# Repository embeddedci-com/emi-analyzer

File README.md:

# EMI Analyzer

PCB EMI and EMC analysis on your own computer. Open a KiCad board or a zip of Gerber files and
see what to fix, marked on the board, in seconds.

| | |
|---|---|
| **Layout checks** | 23 checks: return paths, plane gaps and stitching, decoupling, impedance, length matching, differential pair routing, test point stubs, copper under antennas, thin power traces, ESD protection at connectors, shield grounding, reset lines, power input and switching-regulator layout. Each finding says what to do. |
| **Decoupling** | Per supply rail and IC: the impedance of its capacitors against a target, where it falls short, and which change closes the gap. |
| **ESD** | An IEC 61000-4-2 contact discharge into each line that leaves the board, simulated in ngspice, with the clamp where it is and moved to the connector. |
| **Cables** | How much common-mode current each connector's cable can carry before it passes the FCC limit, from an antenna model in nec2c. |
| **Part solve** | One net (or a pair) cut out over its planes and solved in openEMS in minutes: where its current flows and what its ends see. No far field, no compliance estimate, no coupling into neighboring nets, and no component models (those need `full-wave` and the openEMS the worker image ships). See [verification](docs/verification/small-part-solve.md). |
| **Versions** | Upload a changed layout as a new version and see which findings were fixed and which are new. |
| **Settings** | Turn checks on or off and set thresholds per board in the app, or in an `emi.rules.yaml` next to the board. |
| **Reports** | One HTML file (or PDF) with the board, findings and results, to share. |

Your boards and results stay on your computer. Nothing is uploaded anywhere.

Results are for comparing versions of your own board. They are not a pre-compliance test. See
[known issues](docs/known-issues.md).

Full-wave simulation of a whole region (openEMS) and conducted emissions are built but off. See
[experimental features](#experimental-features).

---

## Contents

1. [What you need](#what-you-need)
2. [Step 1: Install Docker](#step-1-install-docker)
3. [Step 2: Install EMI Analyzer](#step-2-install-emi-analyzer)
4. [Step 3: First launch](#step-3-first-launch)
5. [Step 4: Analyze a board](#step-4-analyze-a-board)
   - [Sharing results](#sharing-results)
6. [Using it from KiCad](#using-it-from-kicad)
7. [Using it from Claude Code](#using-it-from-claude-code)
8. [Running without the desktop app](#running-without-the-desktop-app)
9. [Running in the background](#running-in-the-background)
10. [Where your data is](#where-your-data-is)
11. [Updating and uninstalling](#updating-and-uninstalling)
12. [Troubleshooting](#troubleshooting)
13. [Experimental features](#experimental-features)
14. [More documentation](#more-documentation)

---

## What you need

| | |
|---|---|
| **Operating system** | macOS 11 or newer (Apple Silicon or Intel), Windows 10 or 11 (64-bit), or 64-bit Linux on x86-64 |
| **Memory** | 8 GB or more |
| **Disk** | About 4 GB free: 1.4 GB for the worker image, the rest for Docker and your results |
| **Docker** | Docker Desktop on macOS and Windows; Docker Engine or Docker Desktop on Linux |
| **Internet** | Only to download the app and, once per version, the worker image |

EMI Analyzer has two parts. The **app** is a small download that shows your boards and results.
The **worker** does the analysis. It runs inside Docker, so it behaves the same on every
operating system, and the app starts and stops it for you.

---

## Step 1: Install Docker

Skip this step if `docker ps` already works in a terminal.

### macOS

With [Homebrew](https://brew.sh), one command:

```bash
brew install --cask docker-desktop
```

Then continue at step 3. Without Homebrew:

1. Download **Docker Desktop for Mac** from
   <https://docs.docker.com/desktop/setup/install/mac-install/>. Choose **Apple Silicon** or
   **Intel** to match your Mac (Apple menu → *About This Mac* → *Chip* or *Processor*).
2. Open the downloaded `Docker.dmg` and drag **Docker** into **Applications**.
3. Open **Docker** from Applications. Accept the service agreement and, when asked, allow the
   helper with your password.
4. Wait until the Docker whale in the menu bar stops animating.
5. Check it in Terminal:

   ```bash
   docker ps
   ```

   A header line with nothing under it means Docker is ready.

[OrbStack](https://orbstack.dev) works too, instead of Docker Desktop.

### Windows

1. Open **Terminal as Administrator** (right-click the Start button → *Terminal (Admin)*) and
   install the Windows Subsystem for Linux:

   ```powershell
   wsl --install
   ```

   Restart the computer when it finishes.
2. Download **Docker Desktop for Windows** from
   <https://docs.docker.com/desktop/setup/install/windows-install/> and run the installer. Keep
   **Use WSL 2 instead of Hyper-V** selected.
3. Sign out and back in if the installer asks, then start **Docker Desktop** from the Start menu
   and accept the service agreement.
4. Wait until Docker Desktop shows **Engine running**.
5. Check it in a new terminal:

   ```powershell
   docker ps
   ```

   A header line with nothing under it means Docker is ready.

### Linux (Ubuntu or Debian)

1. Install Docker Engine by following <https://docs.docker.com/engine/install/ubuntu/>, or the
   page for your distribution. On Ubuntu, Docker's install script does it in one step:

   ```bash
   curl -fsSL https://get.docker.com | sh
   ```

2. Let your user run Docker without `sudo`, which the app needs:

   ```bash
   sudo usermod -aG docker $USER
   ```

3. **Log out and log back in** (or restart) so the change takes effect.
4. Check it:

   ```bash
   docker ps
   ```

   A header line with nothing under it means Docker is ready. *Permission denied* means you have
   not logged out and back in since step 2.

---

## Step 2: Install EMI Analyzer

**On a Mac, use Homebrew.** One command installs the app and gets it past macOS's check for
apps that are not code-signed:

```bash
brew trust embeddedci-com/tap
brew install --cask embeddedci-com/tap/emi-analyzer
```

Recent versions of Homebrew ask you to trust a tap before they load anything from it.

Then open **EMI Analyzer** from Applications. Update it later with
`brew upgrade --cask embeddedci-com/tap/emi-analyzer`. No Homebrew? Install it from <https://brew.sh>, or use the
`.dmg` below.

For other computers, or a Mac without Homebrew, go to the [latest release](https://github.com/embeddedci-com/emi-analyzer/releases/latest) and
download the file for your computer:

| Computer | Download |
|---|---|
| Mac with Apple Silicon (M1, M2, M3, …) | `EMI.Analyzer_<version>_aarch64.dmg` |
| Mac with an Intel processor | `EMI.Analyzer_<version>_x64.dmg` |
| Windows | `EMI.Analyzer_<version>_x64-setup.exe` (or the `.msi`) |
| Ubuntu / Debian | `EMI.Analyzer_<version>_amd64.deb` |
| Fedora / RHEL | `EMI.Analyzer-<version>-1.x86_64.rpm` |
| Other Linux | `EMI.Analyzer_<version>_amd64.AppImage` |

The installers are **not code-signed** yet, so your operating system warns you the first time you
open the app. That is expected; here is how to get past it.

### macOS (`.dmg`)

Skip this if you installed with Homebrew.

1. Open the downloaded `.dmg` and drag **EMI Analyzer** into **Applications**.
2. Open **EMI Analyzer** from Applications. macOS says it cannot verify the developer: click
   **Done**, not *Move to Trash*.
3. Open **System Settings → Privacy & Security**, scroll to the message about EMI Analyzer, click
   **Open Anyway**, and confirm with your password.
4. If macOS instead says the app **"is damaged and can't be opened"**, that is the same check
   worded differently. Remove the download quarantine in Terminal and open the app again:

   ```bash
   xattr -dr com.apple.quarantine "/Applications/EMI Analyzer.app"
   ```

### Windows

1. Run the downloaded `-setup.exe`.
2. Windows SmartScreen shows **"Windows protected your PC"**. Click **More info**, then
   **Run anyway**.
3. Follow the installer. It installs Microsoft WebView2 if your computer does not have it yet.
4. Start **EMI Analyzer** from the Start menu.

### Ubuntu / Debian (`.deb`)

```bash
sudo apt install ./EMI.Analyzer_*_amd64.deb
```

Start **EMI Analyzer** from your applications menu.

### Fedora / RHEL (`.rpm`)

```bash
sudo dnf install ./EMI.Analyzer-*-1.x86_64.rpm
```

Start **EMI Analyzer** from your applications menu.

### Other Linux (`.AppImage`)

AppImages need FUSE. On Ubuntu 24.04 install it with `sudo apt install libfuse2t64`, on older
releases with `sudo apt install libfuse2`. Then make the file executable and run it:

```bash
chmod +x EMI.Analyzer_*_amd64.AppImage
```

```bash
./EMI.Analyzer_*_amd64.AppImage
```

---

## Step 3: First launch

1. **Make sure Docker is running** (Step 1).
2. **Open EMI Analyzer.** A window opens on the analyzer's home page.
3. **Watch the badge in the top-right corner.** On the first launch it says
   **Downloading worker** while Docker pulls `ghcr.io/embeddedci-com/emi-worker:<version>`, about
   330 MB to download and 1.4 GB on disk. That takes a few minutes and happens once per app
   version.
4. When the badge turns green and says **Worker running**, the app is ready.

Click the badge at any time to see the worker's log or restart it.

The worker container starts when you open the app and is removed when you close it. Nothing keeps
running in the background.

---

## Step 4: Analyze a board

1. On the home page, drop a board file on the upload area, or click **Choose a file**, and pick
   one of:
   - a `.kicad_pcb` file;
   - a zipped KiCad project;
   - a zip of Gerber files **including the drill file and an IPC-D-356 netlist**: Gerbers carry
     no net names on their own.

   No board to hand? Click **Try the sample board**.
2. The board appears within a few seconds, with each finding marked and numbered on it and the
   **Findings** tab on the right. Click a marker to open its finding, or a finding to zoom to it.
3. Look at the other tabs:
   - **ESD**: simulate a discharge into a connector's lines, and compare the voltage at the IC pin
     with the clamp where it is against the clamp moved to the connector.
   - **Cables**: the board's connectors, each with a suggested cable. Click **Get budgets** to
     see each cable's common-mode budget.
   - **Board**: stackup, nets and layer settings.
4. Opening the same file again takes you to the existing project instead of creating a new one.
5. Changed the layout? In the **⋯** menu, click **Upload a new version** and pick the changed file.
   It becomes version 2 of the same board, and a version picker appears in the header.
6. Click **Compare** in the header to see two versions side by side: which findings were fixed
   and which are new, which nets changed length or via count, and, when both versions have run
   them, the cable budgets and the ESD peak at each pin. A version without a cable or ESD run
   offers to run it with the other version's settings.
7. The header also has **Runs**, which lists what has been analyzed and lets you retry anything
   that failed, and the **⋯** menu can rename the board, delete one version, or delete the board
   with every version. Deleting removes the files and results from this computer.
8. To share results, see [Sharing results](#sharing-results).

### Sharing results

Click **Export report** in the board header. Pick the sections (all that are available are on)
and the format, check the preview, and download.

- **HTML report**: one file with everything inline, for your team or a test lab. It has a title
  page (board, version, date, app and worker versions, file hash, stackup, the rules file and
  settings used, which experimental features were on), the board with numbered finding markers,
  the findings by severity and rule, the analysis notes, and, when they have been run, the cable
  budgets and ESD results with their charts and a "changes since version N" section. It loads
  nothing from the network. To get a PDF, open it in a browser and print it, or click **Print or
  save as PDF** in the dialog.
- **JSON data**: the same content, for scripts and CI.

A cable or ESD run that has not been done on this version is listed in the dialog with a **Run
now** button, and named in the report as not included. Every report says, on its first page and
on each printed page, that it compares versions of your own board and is not a pre-compliance
test.

---

## Using it from KiCad

There is a KiCad plugin that puts all of this beside the PCB Editor: it hands the app the board
you have open, unsaved edits and all, and clicking a finding selects that net on the board.

Install the app first (the plugin is only a front end for it), then in KiCad open
**Plugin and Content Manager → Manage repositories** and add

```
https://raw.githubusercontent.com/embeddedci-com/kicad-plugins/main/repository.json
```

then install **EMI Analyzer** from it. Details and troubleshooting:
[kicad-plugin/README.md](kicad-plugin/README.md).

**The app does not have to be on screen.** Press **Minimize to menu bar** in its header
(**Minimize to tray** on Windows and Linux), or close its window, and it carries on serving the
plugin with your boards, results and worker untouched. Open it again, or quit it, from that
icon's menu. The plugin also starts the app by itself when it is not running.

## Using it from Claude Code

The app includes an MCP server, `emi-local mcp`, so a coding agent can review a board for you:
analyze it, read what the checks found, judge each finding against the board, and compare two
versions after a fix. It talks to the app on your computer (starting it when it is not up), so
the boards it analyzes show up in the app's window too. Nothing leaves your computer.

For Claude Code, add the EmbeddedCI plugin marketplace and install the plugin:

```bash
claude plugin marketplace add embeddedci-com/benchpod-mcp
```

```bash
claude plugin install emi-analyzer@benchpod-mcp
```

Then ask, for example, "review ~/boards/amp/amp.kicad_pcb for EMI problems". The plugin's
`emi-review` skill has the agent check each finding against the board (what a net carries, what
a pin is, whether a connector leaves the enclosure) and report the real problems with fixes.

Any other MCP client can run the server directly: the command is `emi-local mcp`, on macOS
`"/Applications/EMI Analyzer.app/Contents/MacOS/emi-local" mcp`. It reads two environment
variables: `EMI_ANALYZER_URL` to use an app you started yourself (and never start one), and
`EMI_ANALYZER_MCP_STATE` to keep its memory of which project each board file became somewhere
other than the app's config folder.

| Tool | What it does |
|---|---|
| `status` | The app, its version and data folder, and how its Docker worker is doing |
| `analyze_board` | Analyze a `.kicad_pcb` (with its `.kicad_pro` and `emi.rules.yaml`), a project folder, a Gerber folder or a `.zip`; each new upload is a version of the board's project |
| `run_status` | A run's progress, waiting for it when asked |
| `list_projects`, `list_versions` | Projects, and a project's versions with their analyses |
| `findings`, `finding` | What the checks found, filtered and paginated, and one finding in full |
| `decoupling`, `nets` | Supply impedance per rail and IC, and per-net lengths, delays and skew. Experimental: `decoupling` with `rail` or `ic` and `impedance` (or `impedance_hz` for chosen frequencies) also returns \|Z\| at the IC's supply pins, as laid out and with each recommended change applied: a lumped estimate from the layout, 100 kHz to 1 GHz (`impedance_hz` also takes 10 to 100 kHz, with a warning) |
| `compare` | What changed between two versions: findings fixed and new, nets whose length changed |
| `checks` | The checks, their settings, and the `emi.rules.yaml` format |
| `run_esd`, `esd` | Start and read an ESD simulation of the lines that leave the board |
| `run_cables`, `cables` | Start and read a cable budget for the board's connectors |
| `open_in_app` | A link to a version or a comparison in the app |

---

## Running without the desktop app

The desktop app is a window around one program, `emi-local`, which also runs on its own and opens
the analyzer in your browser. Use it on a Linux machine without a desktop, or if you prefer a
browser tab. You still need Docker (Step 1).

1. Download `emi-local-<version>-<os>-<arch>` from the
   [latest release](https://github.com/embeddedci-com/emi-analyzer/releases/latest).
2. On macOS and Linux, make it executable:

   ```bash
   chmod +x emi-local-*
   ```

   On macOS, also remove the download quarantine, for the same reason as the app:

   ```bash
   xattr -d com.apple.quarantine emi-local-*
   ```

3. Run it (the file name depends on what you downloaded):

   ```bash
   ./emi-local-0.1.0-linux-amd64
   ```

   It prints its address and opens it in your browser: `http://127.0.0.1:7465`, or the next free
   port if that one is taken. Stop it with **Ctrl+C**, which also removes the worker container.

It only listens on this computer. To use it from another machine, forward the port over SSH
instead of exposing it, because the app has no sign-in:

```bash
ssh -L 7465:127.0.0.1:7465 your-server
```

| Flag | Default | |
|---|---|---|
| `-data-dir` | see below | where boards, results and the database are kept |
| `-open=false` | opens | do not open a browser tab |
| `-addr` | `127.0.0.1:7465` | listen address; loopback addresses only |
| `-worker none` | `docker` | do not start a worker; [run your own](docs/running-a-worker.md) |
| `-worker-image` | `ghcr.io/embeddedci-com/emi-worker:<version>` | run a different worker image (`:dev` for a build from source) |
| `-worker-concurrency` | `1` | how many runs the worker takes at once |
| `-experimental` | none | enable [experimental features](#experimental-features) |
| `-endpoint-file` | in your config folder | where it says it is listening, so the KiCad plugin can find it; empty writes none |
| `-issue-key` | | print a key for a worker you run yourself, and exit |
| `-version` | | print the version and exit |

`emi-local` serves the [KiCad plugin](kicad-plugin/README.md) as well as the app does. Leave
`emi-local -open=false` running and the plugin finds it.

---

## Running in the background

EMI Analyzer keeps working with its window put away: closing the window does not quit it, and
neither does **Minimize to menu bar** in the header, which reads **Minimize to tray** on Windows
and Linux. The server, your boards and the Docker worker all stay up, which is what the
[KiCad plugin](kicad-plugin/README.md) needs when the PCB Editor is the front end.

Its icon stays in the menu bar on macOS, the notification area on Windows and the system tray
on Linux. That menu has **Open EMI Analyzer** and **Quit**. Quit is the only thing that stops
the worker container.

---

## Where your data is

| | Desktop app | `emi-local` on its own |
|---|---|---|
| macOS | `~/Library/Application Support/com.embeddedci.emi-analyzer` | `~/Library/Application Support/emi-analyzer` |
| Windows | `%APPDATA%\com.embeddedci.emi-analyzer` | `%APPDATA%\emi-analyzer` |
| Linux | `~/.local/share/com.embeddedci.emi-analyzer` | `~/.config/emi-analyzer` |

The folder holds `emi.db` (projects, runs and components, in SQLite), `blobs/` (your board files
and results) and `secret.key` (signs this installation's download links and worker keys). Back up
the folder to keep your projects; delete it to start over. To remove one board and its results,
use **⋯ → Delete this board** in the app.

---

## Updating and uninstalling

**Update:** download and install the newer release over the old one. Your data folder is kept. The
new version downloads its own worker image on first launch. To reclaim disk, list the old images
and remove the ones you no longer need:

```bash
docker image ls ghcr.io/embeddedci-com/emi-worker
```

```bash
docker image rm ghcr.io/embeddedci-com/emi-worker:<old-version>
```

**Uninstall:**

1. Remove the app: `brew uninstall --cask embeddedci-com/tap/emi-analyzer` or drag it from Applications to the Bin (macOS), use *Settings → Apps* (Windows),
   run `sudo apt remove emi-analyzer` (`.deb`), or delete the AppImage.
2. Delete the data folder listed above.
3. Remove the worker images:

   ```bash
   docker image rm $(docker image ls -q ghcr.io/embeddedci-com/emi-worker)
   ```

---

## Troubleshooting

| What you see | What to do |
|---|---|
| **Docker not installed**, but it is | The app looks on your `PATH` and in the usual install locations. Start the app from a terminal where `docker ps` works, or use `emi-local`. |
| **Docker not running** | Start Docker Desktop, or run `sudo systemctl start docker` on Linux. The worker starts by itself a few seconds later. |
| **Downloading worker** never finishes | Check your connection and free disk space, then click the badge → **Restart worker**. Behind a proxy, set it in Docker Desktop → *Settings* → *Resources* → *Proxies*. |
| **Worker stopped** | Click the badge and read the log. On Linux, check that `docker ps` works without `sudo` (Step 1). |
| Worker running, but a board never finishes processing | The worker cannot reach the app. With an unusual Docker setup, run `emi-local -worker-url http://<address>:7465`, where the address is how containers reach your computer. |
| **"Interrupted: the app was closed"** on a run | Runs do not survive closing the app. Retry the run. |
| macOS: **"EMI Analyzer is damaged"** | See Step 2 → macOS → item 4. |
| The Linux AppImage does nothing | Install FUSE (Step 2), or use the `.deb`. |

Found a bug? Open an issue at <https://github.com/embeddedci-com/emi-analyzer/issues> and include
the worker log from the badge.

---

## Experimental features

Some features are built but not yet reliable, and are switched off. Off means the app refuses to
run them, not just that the buttons are hidden.

| Name | What it enables | Why it is off |
|---|---|---|
| `full-wave` | openEMS full-wave simulation of a board region, hotspot maps, the far field, cable emissions and the compliance estimate: the Solve, Drivers, Components, Results and Compliance tabs | It runs, and a test board solves end to end. What has not been done is verifying any of it on a real board, or at the record length a radiated result needs. Treat anything it produces as unchecked. See [known issues](docs/known-issues.md). |
| `conducted` | A conducted-emissions scan of the power input with ngspice, on the Conducted tab: two LISNs, the input filter as laid out and each buck regulator as a current source, against FCC 15.107. Differential mode only | The LISN, a buck's input ripple and an LC filter match closed forms, but no board has been compared with a measurement, and regulator settings are assumed until you enter them. See [verification](docs/verification/conducted-emissions.md). |

To try one anyway, set `EMI_EXPERIMENTAL` to its name where the app is started (a
comma-separated list for more than one). For `full-wave`:

- **`emi-local`:**

  ```bash
  ./emi-local -experimental full-wave
  ```

- **Desktop app on macOS:**

  ```bash
  EMI_EXPERIMENTAL=full-wave "/Applications/EMI Analyzer.app/Contents/MacOS/emi-analyzer"
  ```

- **Desktop app on Windows:** add a user environment variable `EMI_EXPERIMENTAL` with the value
  `full-wave` (Start → *Edit environment variables for your account*), then start the app.
- **Desktop app on Linux:** `EMI_EXPERIMENTAL=full-wave emi-analyzer`.

Full-wave simulation needs a lot of memory and CPU. On macOS and Windows, give Docker as much
memory as you can spare under Docker Desktop → *Settings* → *Resources*.

---

## More documentation

| | |
|---|---|
| [docs/known-issues.md](docs/known-issues.md) | What is verified, what is experimental, what is not built yet |
| [docs/running-a-worker.md](docs/running-a-worker.md) | Running the worker yourself: on another machine, or from source |
| [docs/rules-file.md](docs/rules-file.md) | Tuning the checks for a board with a rules file |
| [docs/emi-driver-format.md](docs/emi-driver-format.md) | The driver file format |
| [docs/](docs/README.md) | Everything else: how the model works, and design notes |
| [kicad-plugin/README.md](kicad-plugin/README.md) | The KiCad plugin: installing it, using it, and how it works |
| [CONTRIBUTING.md](CONTRIBUTING.md) | Building from source, tests, and releasing |

## Security

The app has no sign-in, so it protects itself by where it listens and who may call it. It binds
only to loopback addresses; answers only requests addressed to `localhost` or `127.0.0.1`, which
stops web pages reaching it through DNS rebinding; refuses changes requested by any other origin,
including other ports on this computer, and changes not sent as JSON; cannot be framed by other
sites; serves files only on links signed with a per-installation secret that expire after 15
minutes; and gives the worker a key that is revoked when the app stops. To report a vulnerability, see [SECURITY.md](SECURITY.md).

## License

[Apache License 2.0](LICENSE). The worker image also contains third-party programs under their own
licenses, notably openEMS (GPL-3.0), nec2c (GPL-2.0) and ngspice (BSD), which it runs as separate
programs. [worker/NOTICE](worker/NOTICE) lists them and says where their source code is.

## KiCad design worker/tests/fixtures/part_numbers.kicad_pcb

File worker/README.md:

# EMI worker

The part of the EMI Analyzer that does the work: parses the board, runs the geometric checks,
simulates ESD discharges and cable budgets, meshes a region and calls openEMS, and uploads the
results.

It **dials out**: it opens a WebSocket to the app, says what it can do, and is handed runs over
that connection. It **keeps nothing**: its identity is a key in its environment, and its disk is
one scratch directory per run, deleted when the run ends.

The app starts this worker in Docker by itself. To run one yourself (on another machine, or from
source), see [docs/running-a-worker.md](../docs/running-a-worker.md).

## Develop on it

```bash
python3 -m venv .venv && .venv/bin/pip install -e '.[dev]'
```

```bash
.venv/bin/pip install --no-deps "gerbonara>=1.5"
```

```bash
.venv/bin/python -m pytest
```

Tests that need `ngspice`, `nec2c` or openEMS skip where those are missing; run the whole suite in
the image to cover them (see `.github/workflows/test.yml`). A few tests also run against real
boards when `EMI_TEST_BOARDS` names a directory of `<board>/<board>.kicad_pcb` files.

A worker without openEMS says so at registration and is only offered the run kinds it can do, so
it is a useful thing to run rather than a broken one.

## Layout

```
emi_worker/
  runner.py      the run loop: dial out, claim, execute, report
  client.py      HTTP + WebSocket to the app
  config.py      environment, and capability detection (cores, RAM, container limits, tools)
  kicad/         .kicad_pcb parsing -- s-expressions to a normalised board
  gerber/        RS-274X, Excellon and IPC-D-356, and net reconstruction from copper
  rules/         the geometric EMI/EMC checks
  transient/     ESD discharge simulation with ngspice
  cables/        cable budget and antenna model (nec2c)
  drivers/       driver spectra, for re-weighting solve results
  components/    component models and footprint matching
  compliance/    limits tables and the compliance estimate
  openems/       mesh generation, CSX XML, running the solver, reading its output
  stages/        one module per run kind: ingest, solve, transient, cable, compliance
```

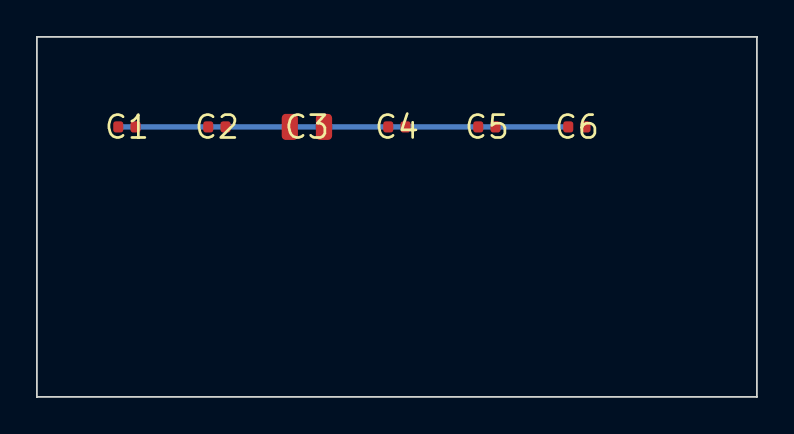
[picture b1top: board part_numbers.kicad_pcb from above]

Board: 2 copper layers, 40.0 x 20.0 mm, 6 parts (0 on the bottom side), 2 nets.

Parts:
C1, C2, C4: 100nF; C_0402_1005Metric
C3: 10u 50V; CAP_2012_custom
C5: 1uF; C_0402_1005Metric
C6: 100nF X7R; C_0402_1005Metric

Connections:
+3V3: C1.1, C2.1, C3.1, C4.1, C5.1, C6.1
GND: C1.2, C2.2, C3.2, C4.2, C5.2, C6.2

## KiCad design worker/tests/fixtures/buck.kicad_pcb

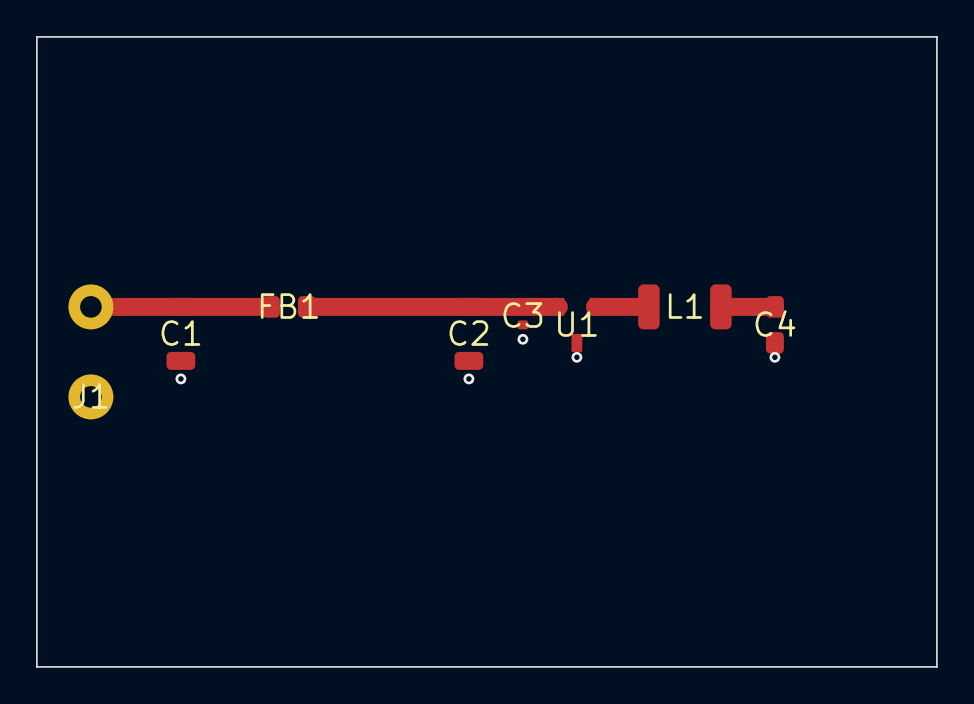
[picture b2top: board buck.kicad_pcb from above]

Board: 2 copper layers, 50.0 x 35.0 mm, 8 parts (0 on the bottom side), 5 nets.

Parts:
C1: 10uF; C_1206_3216Metric
C2: 4.7uF; C_1206_3216Metric
C3: 100nF; C_0402_1005Metric
C4: 22uF; C_0805_2012Metric
FB1: 600R@100MHz; L_0805_2012Metric
J1: Barrel_Jack; BarrelJack_Horizontal
L1: 4.7uH; L_1210_3225Metric
U1: BUCK; SOT-23-6

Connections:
+3V3: C4.1, L1.2
+12V: C1.1, FB1.1, J1.1
/SW: L1.1, U1.2
/VIN: C2.1, C3.1, FB1.2, U1.1
GND: C1.2, C2.2, C3.2, C4.2, J1.2, U1.3

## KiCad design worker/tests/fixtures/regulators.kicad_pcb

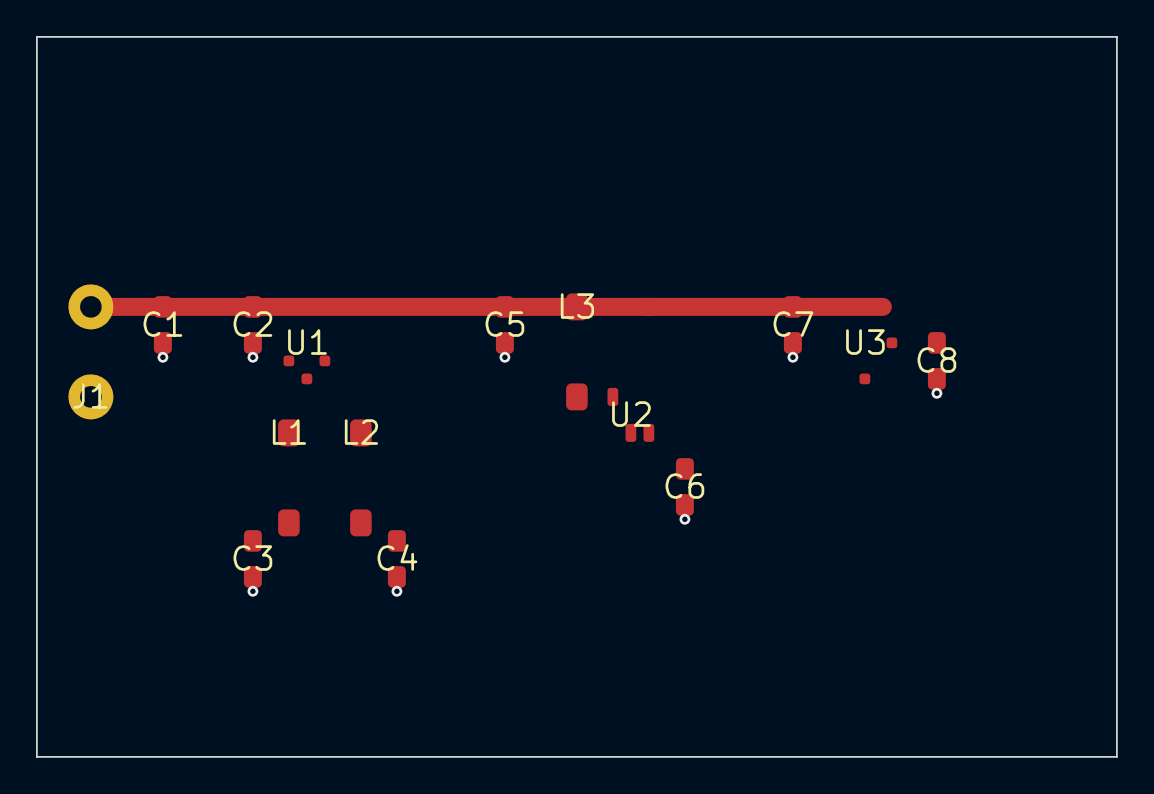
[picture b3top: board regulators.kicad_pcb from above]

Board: 2 copper layers, 60.0 x 40.0 mm, 15 parts (0 on the bottom side), 9 nets.

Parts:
C1: 10uF; C_1206_3216Metric
C2, C5: 4.7uF; C_0805_2012Metric
C3, C4, C8: 22uF; C_0805_2012Metric
C6, C7: 10uF; C_0805_2012Metric
J1: Barrel_Jack; BarrelJack_Horizontal
L1, L2: 2.2uH; L_1210_3225Metric
L3: 22uH; L_1210_3225Metric
U1: PMIC; QFN-16_3x3mm_P0.5mm
U2: MT3608; SOT-23-6
U3: TPS82130SILR; Texas_SIL0008D_MicroSiP-8-1EP_2.8x3mm_P0.65mm

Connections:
+1V8: C4.1, L2.2
+3V3: C3.1, L1.2
+5V: C8.1, U3.4
+12V: C1.1, C2.1, C5.1, C7.1, J1.1, L3.1, U1.1, U1.3, U2.3, U3.1, U3.2
+24V: C6.1, U2.4
/SW3: L3.2, U2.1
GND: C1.2, C2.2, C3.2, C4.2, C5.2, C6.2, C7.2, C8.2, J1.2, U1.5, U2.2, U3.3
unnamed: L1.1, U1.2
unnamed: L2.1, U1.4

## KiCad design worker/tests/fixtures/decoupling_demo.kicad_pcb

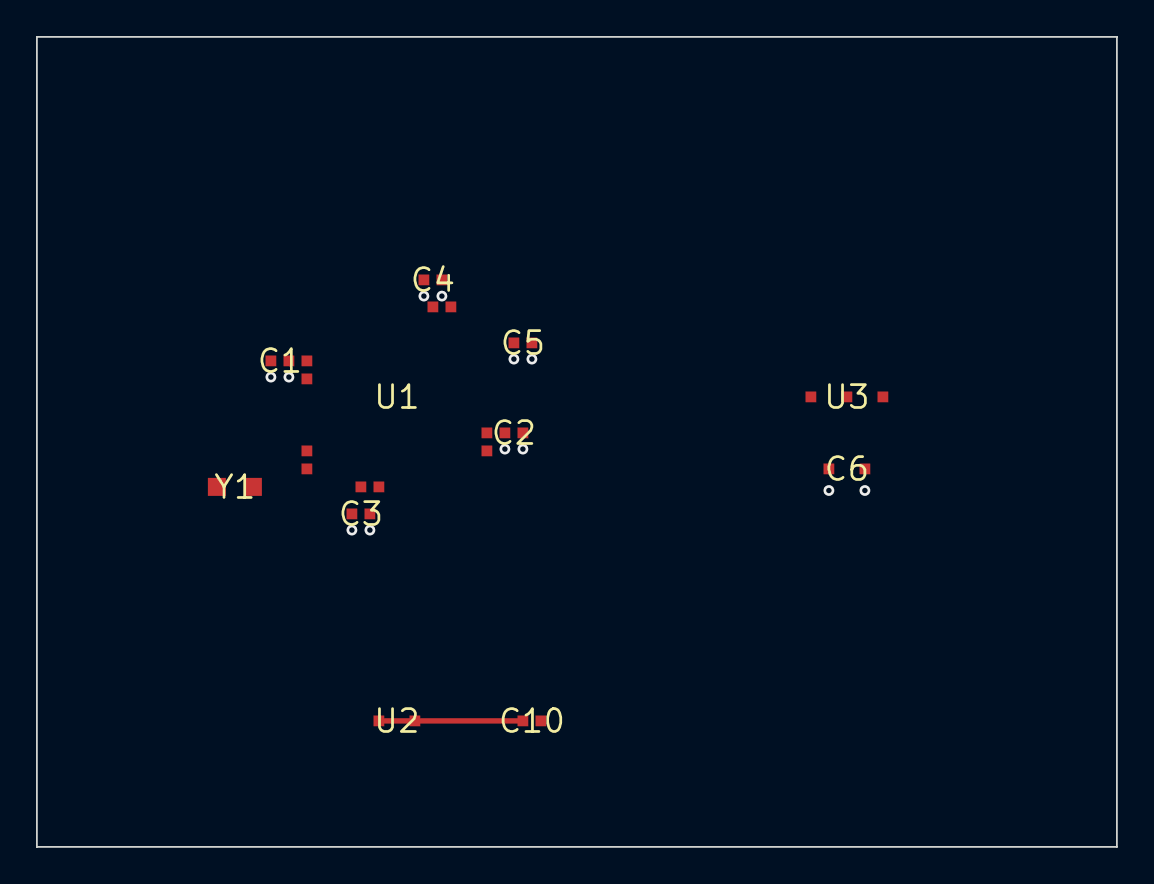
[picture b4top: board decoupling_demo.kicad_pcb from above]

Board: 4 copper layers, 60.0 x 45.0 mm, 11 parts (0 on the bottom side), 5 nets.

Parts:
C1, C2, C3, C4, C10: 100nF; C_0402_1005Metric
C5: 10nF; C_0402_1005Metric
C6: 10uF; C_0805_2012Metric
U1: MCU; LQFP-48
U2: Sensor; WSON-8
U3: LDO 3V3; SOT-223
Y1: 16MHz; Crystal_SMD_3225

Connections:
+1V8: C10.1, U2.1
+3V3: C1.1, C2.1, C3.1, C4.1, C5.1, C6.1, U1.1, U1.3, U1.5, U1.7, U3.2
GND: C1.2, C2.2, C3.2, C4.2, C5.2, C6.2, C10.2, U1.2, U1.4, U1.6, U1.8, U2.2, U3.3
XIN: U1.9, Y1.1
XOUT: U1.10, Y1.2

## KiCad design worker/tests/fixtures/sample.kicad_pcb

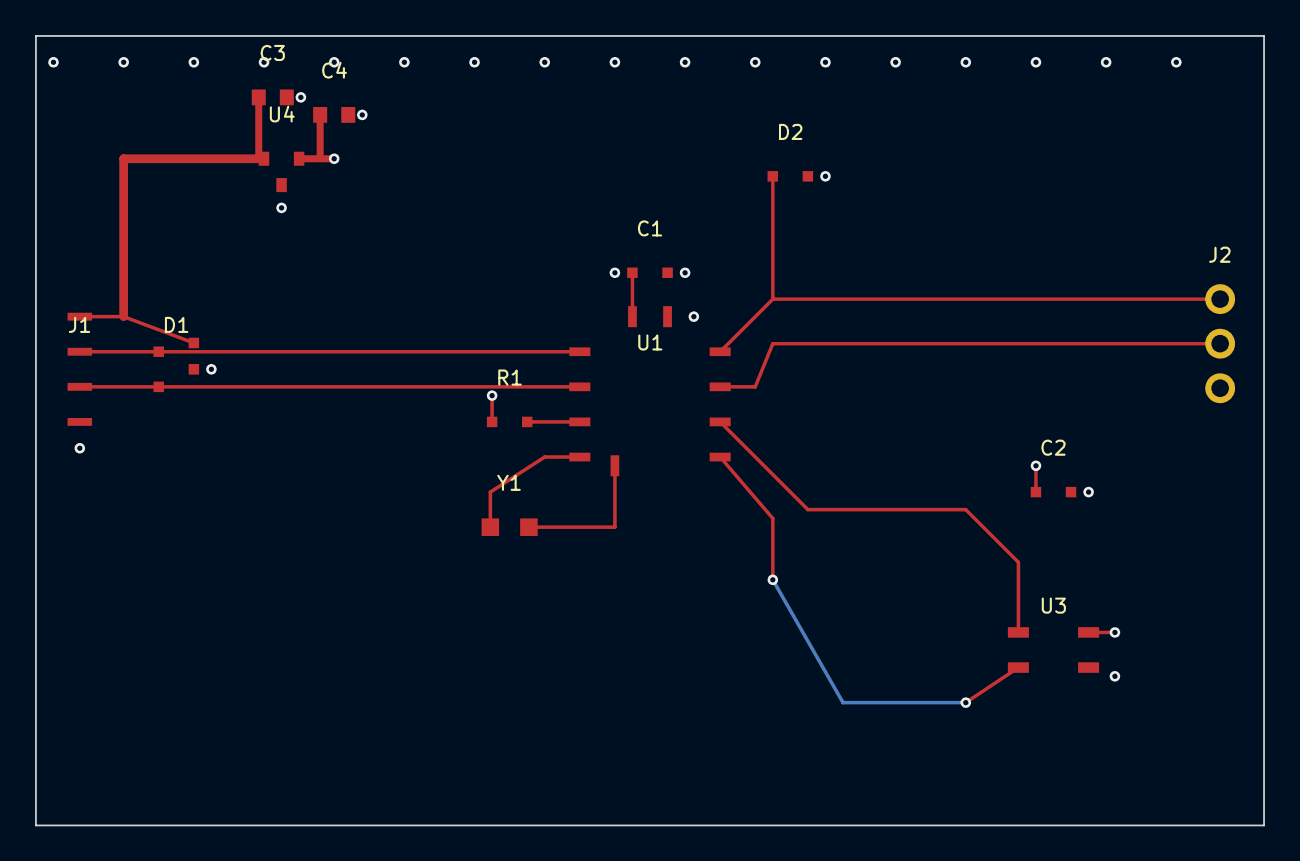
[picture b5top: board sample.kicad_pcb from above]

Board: 4 copper layers, 70.0 x 45.0 mm, 13 parts (0 on the bottom side), 12 nets.

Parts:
C1, C2: 100nF; C_0402_1005Metric
C3, C4: 1uF; C_0603_1608Metric
D1: USBLC6-2SC6; SOT-23-6
D2: PESD5V0S1BA; D_SOD-323
J1: USB_B_Micro; USB_Micro-B_Molex-105017-0001
J2: Conn_01x03; PinHeader_1x03_P2.54mm_Vertical
R1: 10k; R_0402_1005Metric
U1: STM32G031K8; LQFP-32_7x7mm_P0.8mm
U3: W25Q32JVSS; SOIC-8_3.9x4.9mm_P1.27mm
U4: AP2112K-3.3; SOT-23-5
Y1: 16MHz; Crystal_SMD_3225-4Pin_3.2x2.5mm

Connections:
+3V3: C1.1, C2.1, C4.1, R1.1, U1.1, U3.8, U4.5
/NRST: R1.2, U1.5
/SPI_CLK: U1.10, U3.1
/SPI_MOSI: U1.11, U3.2
/UART_RX: J2.2, U1.9
/UART_TX: D2.1, J2.1, U1.8
/USB_DN: D1.1, J1.2, U1.3
/USB_DP: D1.3, J1.3, U1.4
/XIN: U1.6, Y1.1
/XOUT: U1.7, Y1.3
GND: C1.2, C2.2, C3.2, C4.2, D1.2, D2.2, J1.5, J2.3, U1.2, U3.4, U4.2
VBUS: C3.1, D1.5, J1.1, U4.1

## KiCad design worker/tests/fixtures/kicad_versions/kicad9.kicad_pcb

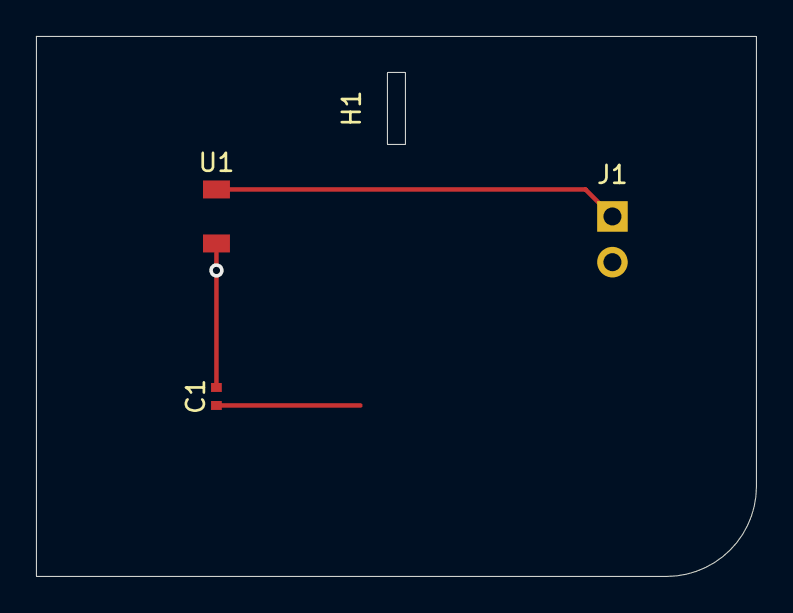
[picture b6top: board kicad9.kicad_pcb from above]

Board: 2 copper layers, 40.0 x 30.0 mm, 4 parts (0 on the bottom side), 2 nets.

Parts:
C1: 100nF; C_0402_1005Metric
H1: Slot; Slot_1x4
J1: Conn_01x02; PinHeader_1x02_P2.54mm_Vertical
U1: CLKGEN; SOT_2pin

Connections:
CLK: J1.1, U1.1
GND: C1.2, J1.2, U1.2
